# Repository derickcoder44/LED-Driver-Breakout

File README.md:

# Teeny Turtles - LED Driver Breakout Board

## Description

LED driver breakout board for UV LED payload used for identifying small, marked
turtles.

## Specifications

See the
[design specification][https://docs.google.com/document/d/1gVzOJjtYFt5bi969M3ABGZ1N9SZz09h7W5uWR9ln1Jk/edit?usp=sharing] 
for more information.

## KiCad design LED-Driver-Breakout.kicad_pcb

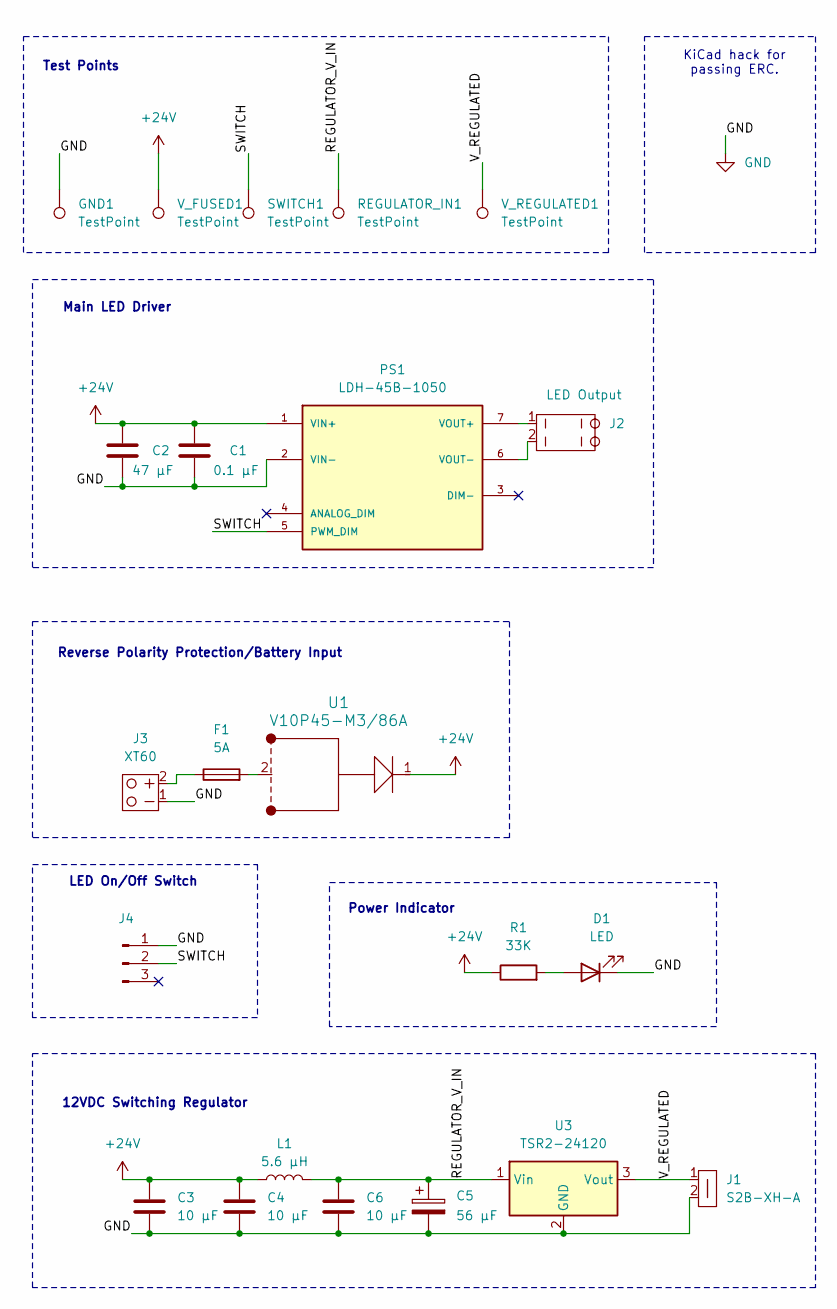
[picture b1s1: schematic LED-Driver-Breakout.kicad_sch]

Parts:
C1: 0.1 µF; C_0805_2012Metric_Pad1.18x1.45mm_HandSolder
C2: 47 µF; C_Elec_6.3x7.7
C3, C4, C6: 10 µF; C_0805_2012Metric_Pad1.18x1.45mm_HandSolder
C5: 56 µF; CP_Elec_8x10
D1: LED; LED_1206_3216Metric_Pad1.42x1.75mm_HandSolder
F1: 5A; 154005DR
GND1: TestPoint; TestPoint_Loop_D2.54mm_Drill1.5mm_Beaded
J1: S2B-XH-A; JST_XH_S2B-XH-A_1x02_P2.50mm_Horizontal
J2: LED Output; TerminalBlock_WAGO_2601-3102_1x02_P3.50mm_Vertical
J3: XT60; AMASS_XT60PW-M_1x02_P7.20mm_Horizontal
J4: 01x03_PinHeaderSwitch; PinHeader_1x03_P2.54mm_Vertical
L1: 5.6 µH; L_0805_2012Metric_Pad1.05x1.20mm_HandSolder
PS1: LDH-45B-1050; PARTREV 2026-03-02
R1: 33K; R_1206_3216Metric_Pad1.30x1.75mm_HandSolder
REGULATOR_IN1: TestPoint; TestPoint_Loop_D2.54mm_Drill1.5mm_Beaded
SWITCH1: TestPoint; TestPoint_Loop_D2.54mm_Drill1.5mm_Beaded
U1: V10P45-M3/86A; D_PowerDI-5
U3: TSR2-24120; Converter_DCDC_TRACO_TSR2-xxxx_THT
V_FUSED1: TestPoint; TestPoint_Loop_D2.54mm_Drill1.5mm_Beaded
V_REGULATED1: TestPoint; TestPoint_Loop_D2.54mm_Drill1.5mm_Beaded

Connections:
+24V: C1.1, C2.1, C3.1, C4.1, L1.1, PS1.1 (VIN+), R1.1, U1.1, V_FUSED1.1
/GND: C1.2, C2.2, C3.2, C4.2, C5.2, C6.2, D1.1 (K), GND1.1, J1.2, J3.1, J4.1, PS1.2 (VIN-), U3.2 (GND); also elsewhere on the board
/REGULATOR_V_IN: C5.1, C6.1, L1.2, REGULATOR_IN1.1, U3.1 (Vin)
/SWITCH: J4.2, PS1.5 (PWM_DIM), SWITCH1.1
/V_REGULATED: J1.1, U3.3 (Vout), V_REGULATED1.1
unnamed: D1.2 (A), R1.2
unnamed: F1.1, J3.2
unnamed: F1.2, U1.2
unnamed: J2.1, PS1.7 (VOUT+)
unnamed: J2.2, PS1.6 (VOUT-)

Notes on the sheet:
Test Points
Reverse Polarity Protection/Battery Input
LED On/Off Switch
12VDC Switching Regulator
Main LED Driver
Power Indicator
KiCad hack for passing ERC.

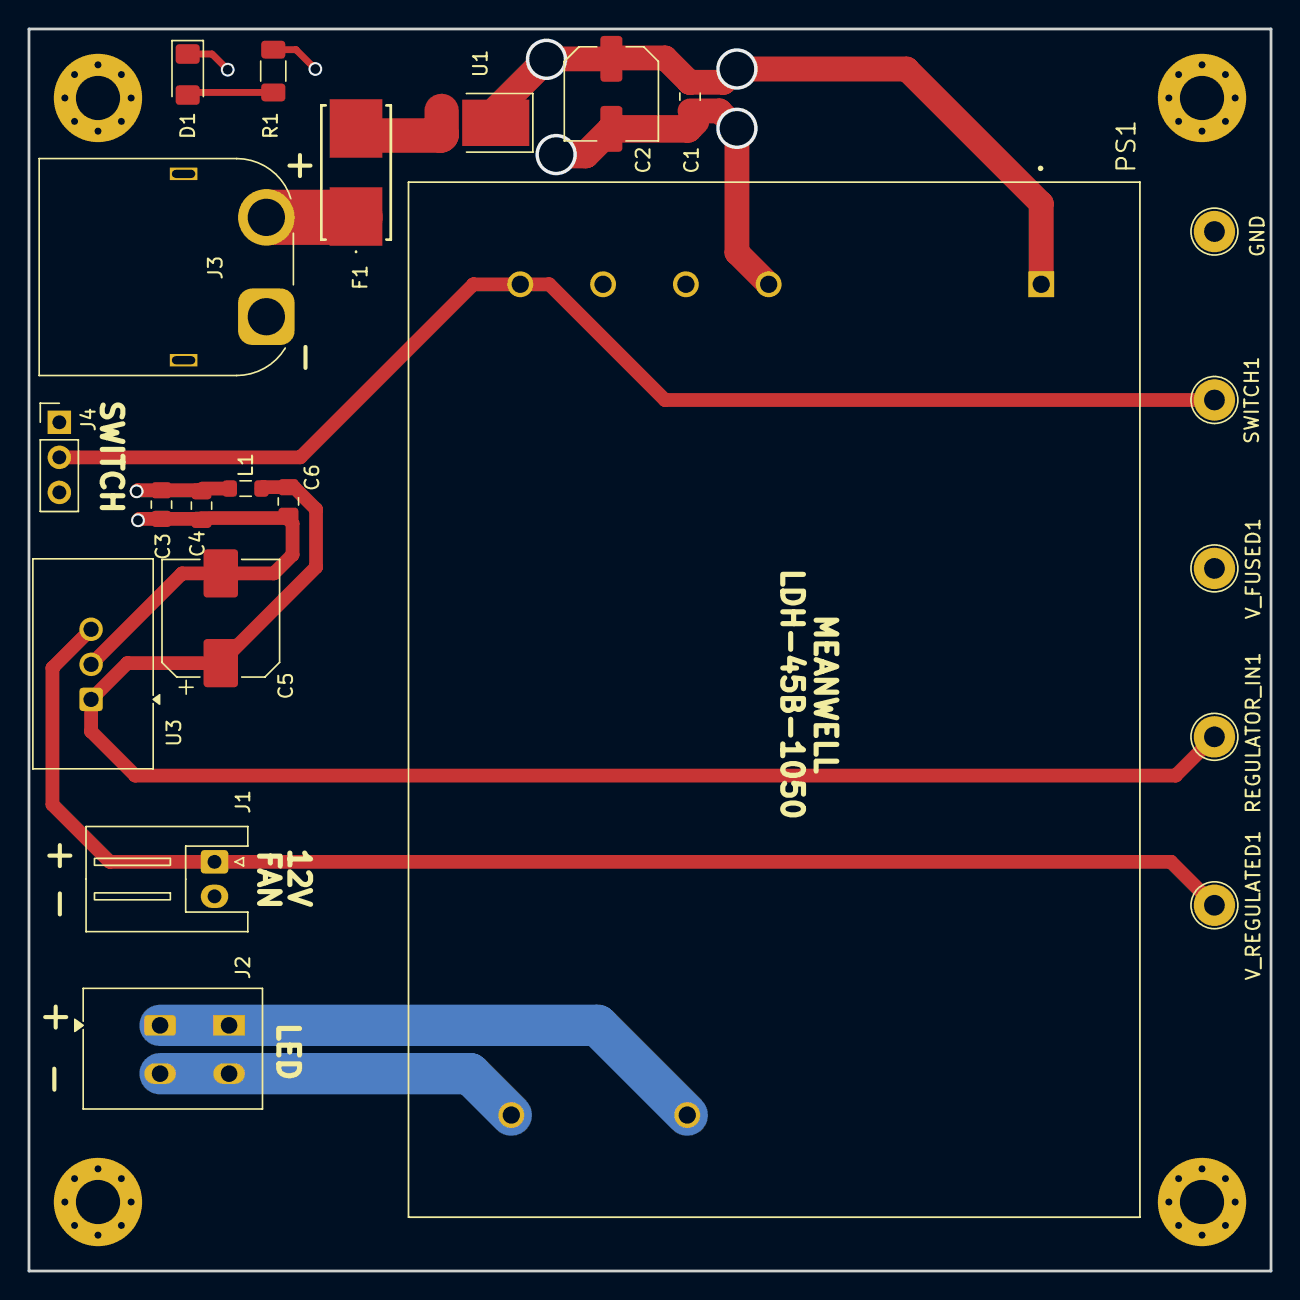
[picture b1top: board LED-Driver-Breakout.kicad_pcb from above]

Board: 4 copper layers, 90.0 x 90.0 mm, 23 parts (0 on the bottom side), 10 nets.

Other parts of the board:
GND: TestPoint; TestPoint_Loop_D2.54mm_Drill1.5mm_Beaded
GND#2: MountingHole_3.2mm_M3_Pad_Via

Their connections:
/GND: GND.1, GND#2.1; also elsewhere on the board

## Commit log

2026-02-06 finished board - need review
2026-02-07 updates based on suggestions
2026-02-09 finished pcb routing may need to make the board more square
2026-02-09 forgot to save from last commit
2026-02-09 made board square only need to add graphics
2026-02-09 forgot to add switch trace
2026-02-24 Added README.
2026-02-26 Updates to schematic.
2026-02-26 Updates trace widths; now realizing the regulator on the schematic is improperly labeled and test points need to be properly made.
2026-03-03 Added project-specific libs/fps; updates generally; broken rn.
2026-03-04 Relayout in progress.
2026-03-24 did layout, still need to fix ERC errors and DRC warnings
2026-03-25 Tiny updates.
2026-03-26 Minor edits to layout to allow passing of ERC.
2026-04-04 added back deisgn
